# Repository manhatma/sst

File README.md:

Sufni Suspension Telemetry
==========================

Sufni\* Suspension Telemetry is a mountain bike suspension telemetry system that
was born out of sheer curiosity. The [data acquisition unit](https://github.com/sghctoma/sst/wiki/02-Data-Acquisition-Unit) is built around the
Raspberry Pi Pico W and uses affordable off-the-shelf components, so anybody
with a bit of soldering skills can build it.

Contrary to most (all?) suspension telemetry systems, Sufni uses rotary encoders
to measure movement. They are cheap, reasonably accurate, and can reach pretty
high sample rates. An additional benefit is that on some frames they are easier
to attach to rear shocks than linear sensors, because they can fit into much
tigther spaces.

The DAQ uses a WiFi network to send recorded sessions to the backend server.
When processing is done, data can be analyzed on the [web user interface](https://github.com/sghctoma/sst/wiki/03-Dashboard) that
provides plots useful for setting up the spring rate, damping and the bike's
overall balance. GPX tracks can also be uploaded, and MP4 videos can be opened
from the local machine. These are synchronized to the travel plot, so you can
easily find how your suspension behaved on a certain part of the trail.

The user interface has two additional functionalities:

 - New bike setups can be created, and they can be associated with a DAQ unit
   based on the Pico's uniqe identifer.
 - Normalized (travel percentage, or a number between 0 and 1) data can also be
   [imported](https://github.com/sghctoma/sst/wiki/04-Importing-normalized-data) from CSV files, so you can use the webapp without being tied to
   Sufni's hardware.

Please refer to the wiki for a [quickstart guide](https://github.com/sghctoma/sst/wiki/01-Quickstart-guide), build instructions, and a full
tour on the user interface, plots etc.

\* *The word "sufni" (pronounced SHOOF-nee) means tool shed in Hungarian, but
also used as an adjective denoting something as DIY, garage hack, etc.*

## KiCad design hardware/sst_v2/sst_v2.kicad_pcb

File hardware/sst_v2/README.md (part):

# SST v2 Mainboard — Rev. 3 (KiCad)

DAQ-Mainboard für Sufni Suspension Telemetry: 24-bit-ADC für Fork- und Shock-Poti,
Takt für vier IMUs, microSD, RTC, Pico 2 W. Entwurfsgrundlage und Begründungen:
`firmware/docs/plan-ads131m04-icm42686.md`.

```bash
open -a "KiCad" /Users/niels/Telemetry/sst/hardware/sst_v2/sst_v2.kicad_pro
```

Nur diesen Ordner bearbeiten. Vor Skript-Änderungen KiCad schließen
(`~*.lck`), sonst überschreibt die GUI beim Speichern.

## Platine

60 × 90 mm, 4 Lagen, 1,6 mm FR4, ENIG. 4× M3-NPTH (H1–H4).

Platzierung:

- Oben: Pico 2 W auf Buchsenleisten, U1 bei (134,4 / 59,8). Der Körper liegt bei x 84,7–137,1 mm. Das Antennenende liegt am linken Platinenrand (Kante 84,5 mm), wie Raspberry Pi es empfiehlt. Das USB-Ende liegt bei x 137,1 mm. Vor dem USB-Ende liegen 7,4 mm Platine (Rand 144,5 mm).
- Links: Poti-Eingang (J_POT1 am Rand, ESD D2–D4, CMCs), darunter Analogblock (LDO, ADC, Opamp, RC-Netz). Der Analogblock liegt weit weg von Funkmodul und SMPS des Pico.
- Mitte: RTC-Batterie BT1 unter dem Pico, Öffnung zum Pico. Der Bereich zwischen BT1 und den Pico-Buchsenleisten ist frei von Bauteilen, damit die Zelle heraus- und hineingleitet.
- Rechts: OLED- und Taster-Stecker am Rand neben ihren Pico-Pins, Buzzer BZ1, Stromversorgung (D1, D_VSYS1, C26), microSD. Der Körper von J_SD1 endet 0,25 mm vor der Platinenkante.
- Oberkante (x 113–123,6 mm, y 48,3–55,2 mm, zwischen Q_RP1 und J_DEBUG1, außerhalb des Pico): Lader U_CHG1 mit C_CHG1/C_CHG2, R_PROG, R_STAT1/R_STAT2. Thermalfläche: Zone „Lader Thermal“ (GND, F.Cu, Priorität 2, volle Anbindung) über den Laderbereich und den Streifen über J_DEBUG1, gefüllt 0,77 cm² zusammenhängend (0,49 cm² im Laderbereich). Sechs GND-Vias 0,6/0,3 mm links neben dem VSS-Pad (Pin 2) zur GND-Lage In1. +VBUS und +VBAT kommen auf B.Cu, F.Cu bleibt dort fast ganz GND.
- Unter dem Pico: R50 (ADC_RST) bei (110,0 / 62,3) neben GP7 (Pin 10). Soft-Power-Steuerung (U_PWR1, C_PWR1, Q_PWR2, Q_PWR3, R_PWR2–R_PWR4, D_PWR1) und Fuel Gauge (U_FG1, C_FG1) zwischen den Buchsenleisten bei x 120–135 mm, y 61–74 mm (Bauhöhe ≤ 1,1 mm, Buchsenleisten 8,5 mm). `sst_v2.kicad_dru` erlaubt die Courtyard-Überdeckung mit U1 nur für diese Teile.
- Unter der unteren Pico-Buchsenleiste (außerhalb des Pico): Lastschalter Q_PWR1 (119,6 / 82,1) mit Gate-Pull-up R_PWR1 (122,9 / 82,1), direkt vor C26.
- Pico-Antenne (Ende gegenüber USB, x < 94 mm, am linken Rand): Rule Area „Pico antenna: keepout“ auf allen Kupferlagen, ohne Leiterbahnen, Vias und Pours. Sie deckt den Raum zwischen den Buchsenleisten (x 84,5–94,0 mm, y 61,3–76,1 mm) und das Pico-Ende über die volle Breite ab (x 84,5–85,1 mm, y 57,1–80,2 mm). Der Rand von 1 mm liegt außerhalb der Platine, die Fläche endet an der Kante. Die Streifen der Buchsenleisten bleiben frei, damit die Leitungen an Pin 17–24 nach außen laufen. In1 (GND) und In2 (+3V3_DIG) haben dort eine Aussparung.
- Fiducials FID1–FID3 (1 mm, Maske 3 mm) auf F.Cu: (135,95 / 54,8), (89,5 / 106,8), (136,95 / 101,3). Alle ≥ 5 mm von der Kante, außerhalb von Pico und Steckern.
- Montagelöcher: Alle Courtyards liegen ≥ 3,5 mm von der Bohrungsmitte (Platz für Schraubenkopf oder Scheibe Ø 7 mm).
- Unten: IMU-Stecker, Taktteiler und Taktpuffer.
- Digitalleitungen (IMU, SD, UI) laufen außerhalb des Analogblocks. Die ADC-SPI-Leitungen laufen im Poti-Block nur auf B.Cu, getrennt durch die GND-Lage In1.

| Lage | Inhalt |
|---|---|
| F.Cu | Bauteile, Signale, GND-Pour |
| In1.Cu | GND, durchgehend |
| In2.Cu | +3V3_DIG; Insel +3V0_ANA unter der analogen Seite von LDO/ADC/Opamp (x 94,3–108,5 mm, y 112,2–132,5 mm, dazu Streifen y 107,8–112,2 mm ab x 84,9 mm). Die digitale Seite von LDO und ADC (x < 94,3 mm) liegt über +3V3_DIG. |
| B.Cu | Signale, GND-Pour |

Fertigungsregeln (PCBWay): Leiterbahn/Abstand ≥ 0,2 mm, Via 0,6/0,3 mm (+3V3_DIG: 0,7/0,4 mm,
Power: 0,8/0,4 mm), Via-Restring ≥ 0,15 mm, Kupfer–Kante ≥ 0,3 mm, Lötstopp-Steg ≥ 0,1 mm
(grüner Lötstopp). Silkscreen: Strichbreite ≥ 0,15 mm, Texthöhe ≥ 0,8 mm (PCBWay-Minimum). `sst_v2.kicad_pro`
prüft Restring und Textstrich mit 0,15 mm, Texthöhe mit 0,8 mm.

## Schaltung

| Block | Bauteile | Kurzbeschreibung |
|---|---|---|
| ADC | U2 ADS131M04 | CH0 Fork, CH1 Shock, CH2 Poti-Speisung (ratiometrisch), CH3 an GND. AVDD 3,0 V, DVDD = Netz +3V3_DVDD aus +3V3_DIG über FB1 (Logikpegel = Pico-Pegel, PWR_FLAG hinter FB1). CAP 220 nF. SYNC/RESET (ADC_RST) über R50 100 Ω an GP7 (ADC_RST_MCU), Pull-up R1, C4. |
| Analog-LDO | U_ANA_LDO1 TPS7A4700 (RGW) | 3,3 V → 3,0 V, ANY-OUT: nur 1P6V (Pin 8) an GND, übrige ANY-Pins offen. SENSE an OUT. NR 10 nF (C25), IN 10 µF (C22), OUT 22 µF (C6). |
| Poti-Speisung | U_AAF1 TLV4333 (A), R32/R33 20k/10k 0,1 %, C35 | 1,0 V Referenz, gepuffert, 47 Ω (R34) auf POT_EXC, Messung über R35/C36 an AIN2P. |
| Schleifer | U_AAF1 (B, C), R36/R37, R8/R14, C9/C12 | Opamp-Puffer, danach 1 kΩ + 10 nF an AINxP. AINxN = Poti-Masse (Remote Sense), R9/R15 0 Ω als Sternpunkt. |
| Poti-Stecker | J_POT1 JST-SH 6 → HR30 6p | 1 POT_EXC, 2 Fork-Schleifer, 3 Fork-Masse, 4 Shock-Schleifer, 5 Shock-Masse, 6 Schirm/GND. ESD D2–D4, CMC L_FORK/L_SHOCK (DLW5BTM251SQ2L). |
| Takt | Y1 ECS-2520MVLC 8,192 MHz, U_DIV1 74HC4040, U_CLKBUF1 74LVC125 | XO → 33 Ω → ADC CLKIN; XO → 4040 Q7 = 32,000 kHz → 2 Puffer → 33 Ω → IMU-CLKIN A/B. |
| IMU | J_IMU_A1/B1 JST-SH 12 → HR30 12p | 1 IMU_3V3 (FB2), 3 SCLK, 5 MOSI, 7 MISO, 8 CLKIN, 10/11 CS, 2/4/6/9/12 GND. 33 Ω in allen DAQ-Ausgängen. |
| Strom | J_BAT1, Q_RP1, Q_PWR1, D1, D_VSYS1 | LiPo (JST-PH) → Q_RP1 DMG2305UX (Verpolschutz) → +VBAT → Q_PWR1 DMG2305UX (Soft-Power-Schalter) → +VBAT_SW (TVS D1, C26–C28) → D_VSYS1 PMEG3020EH → VSYS. D_VSYS1 verhindert, dass USB-VBUS direkt in den Akku speist. Kein externer Schalter mehr (J_PWR1 entfällt). |
| Soft-Power | U_PWR1 MAX16150AUT+T, Q_PWR1 DMG2305UX, Q_PWR2/Q_PWR3 2N7002, R_PWR1–R_PWR4 100k, C_PWR1 100 nF, D_PWR1 RB751S40 | U_PWR1 VCC an +VBAT. Taster SW_L1 → PWR_BTN → PB_IN (interner Pull-up 1,2–2,0 MΩ an VCC). Drücken > 50 ms: OUT (PSW_EN) high → Q_PWR2 zieht PSW_GATE auf GND → Q_PWR1 leitet. R_PWR1 hält Q_PWR1 sonst aus, R_PWR2 hält Q_PWR2 aus, solange OUT undefiniert ist. Aus per Firmware: GP28 (PWR_OFF) high → Q_PWR3 zieht ~CLR low → OUT low. R_PWR4 hält Q_PWR3 ohne Firmware aus. ~CLR-Pull-up R_PWR3 an OUT (Datenblatt-Empfehlung): kein VBAT-Pegel an einem GPIO. Halten > 8 s (Version A): OUT low, Hardware-Aus. ~INT offen. BTN_L (GP4, R27 10k an +3V3_DIG) liegt über D_PWR1 (Anode BTN_L, Kathode PWR_BTN) am Taster: SW_L1 bleibt UI-Taste. |
| Fuel Gauge | U_FG1 MAX17048G+T10, C_FG1 100 nF | VDD (Messeingang) und CELL an +VBAT, dauerhaft versorgt. I2C 0x36 am PIO-I2C (DISP_SDA/DISP_SCL, R25/R26). CTG, QSTRT, EP an GND, ~ALRT offen (kein GPIO frei). |
| Lader | U_CHG1 MCP73831T-2ACI/OT, C_CHG1/C_CHG2 4,7 µF, R_PROG 3,3k, R_STAT1/R_STAT2 10k/10k | Platz an der Oberkante außerhalb des Pico, mit Thermalfläche (GND-Zone 0,77 cm² an VSS, 6 Vias zu In1). VDD an +VBUS (Pico Pin 40), Ausgang an +VBAT (vor dem Schalter): Laden auch bei ausgeschaltetem Gerät (Q_PWR1 offen). 4,20 V, 300 mA (I = 1000 V / R_PROG; 500 mA mit 2,0k). STAT über Teiler 10k/10k an GP6 (CHG_STAT): Laden = 0 V, fertig = 0,5 × VBUS (2,5 V bei 5,0 V, max. 2,6 V bei 5,25 V), ohne VBUS hochohmig → 0 V. USB kommt über ein Kabel von einer Gehäusebuchse in die Micro-USB-Buchse des Pico. |
| RTC | U3 DS3231SN, BT1 CR1220 | VBAT direkt an der Zelle, RST offen. I2C gemeinsam mit OLED und U_FG1 (PIO, R25/R26 4,7k). |
| microSD | J_SD1 DM3AT | SPI0. Pull-ups: SD_CS 10k (R31), DAT1 47k (R48), DAT2 47k (R49). |
| UI | SW_L1/SW_R1 (JST-SH 2), BZ1 PS1240P02BT, J_OLED1, J_DEBUG1 | Taster mit 10k-Pull-up. SW_L1 ist zusätzlich die Power-Taste (siehe Soft-Power). Buzzer über 47 Ω an GP22. J_DEBUG1: 1 RX (GP1), 2 TX (GP0), 3 GND. SWD direkt am Pico. |
| MCU | U1 Pico 2 W | Steckt in 2× 1×20-Buchsenleisten (8,5 mm). 3V3_EN offen (interner Pull-up). |

### Pico-Pinbelegung

| GP | Netz | GP | Netz |
|---:|---|---:|---|
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
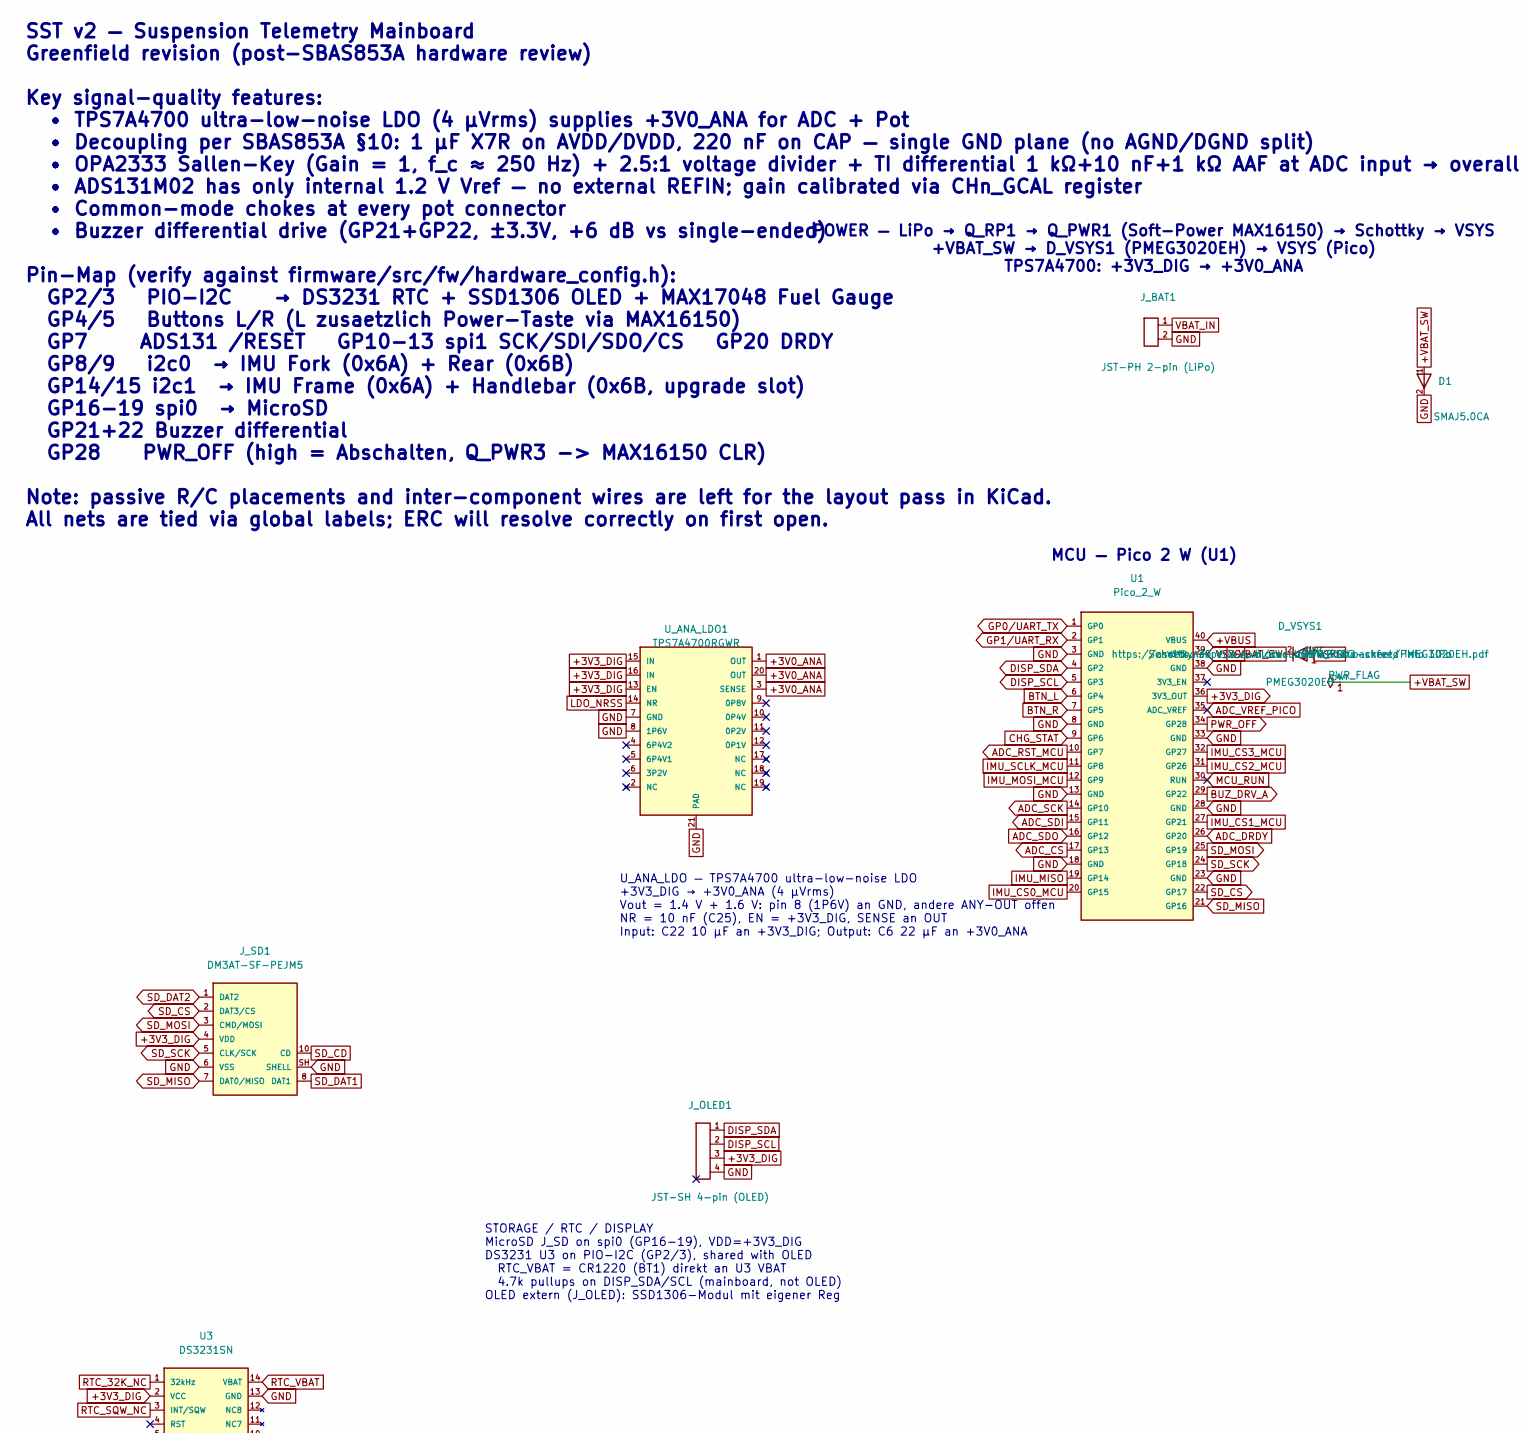
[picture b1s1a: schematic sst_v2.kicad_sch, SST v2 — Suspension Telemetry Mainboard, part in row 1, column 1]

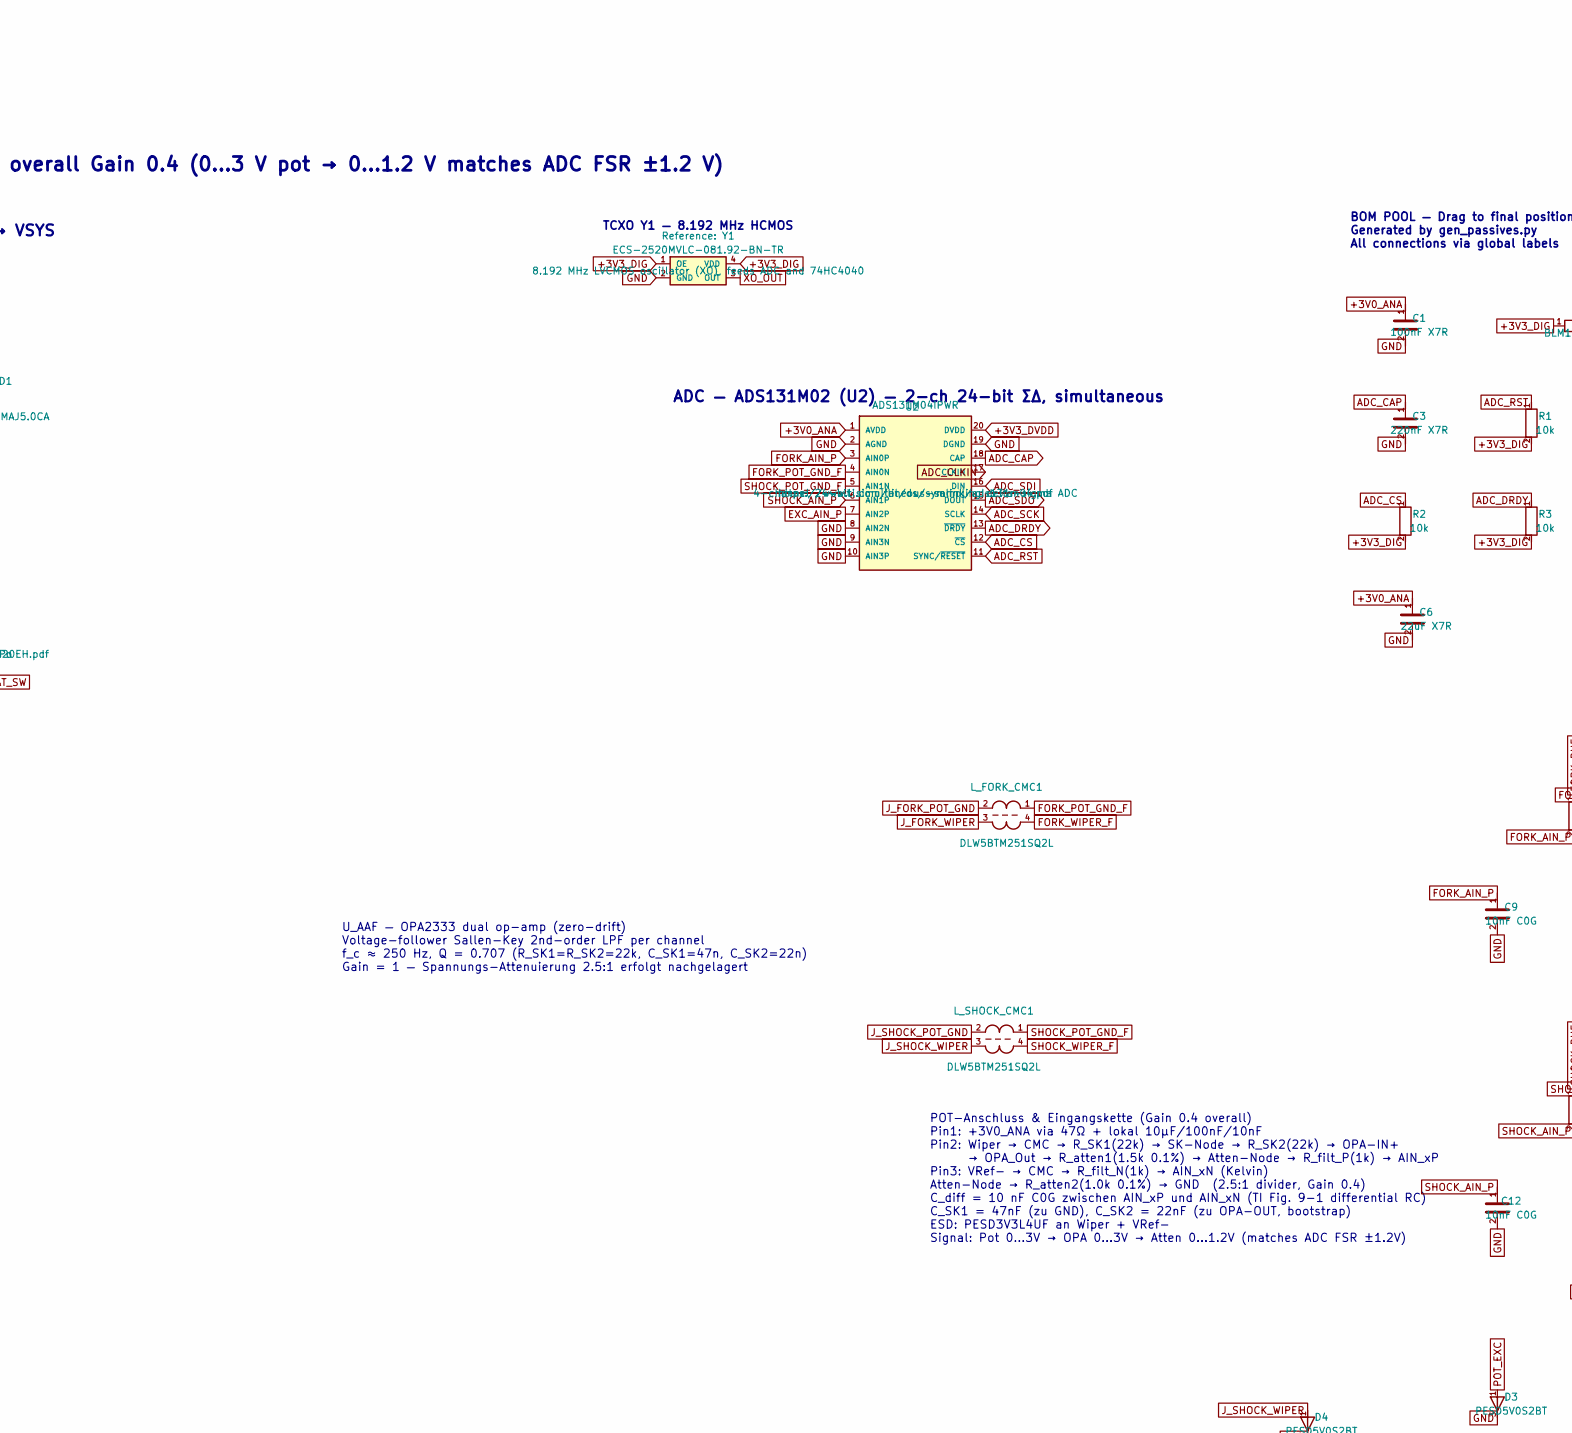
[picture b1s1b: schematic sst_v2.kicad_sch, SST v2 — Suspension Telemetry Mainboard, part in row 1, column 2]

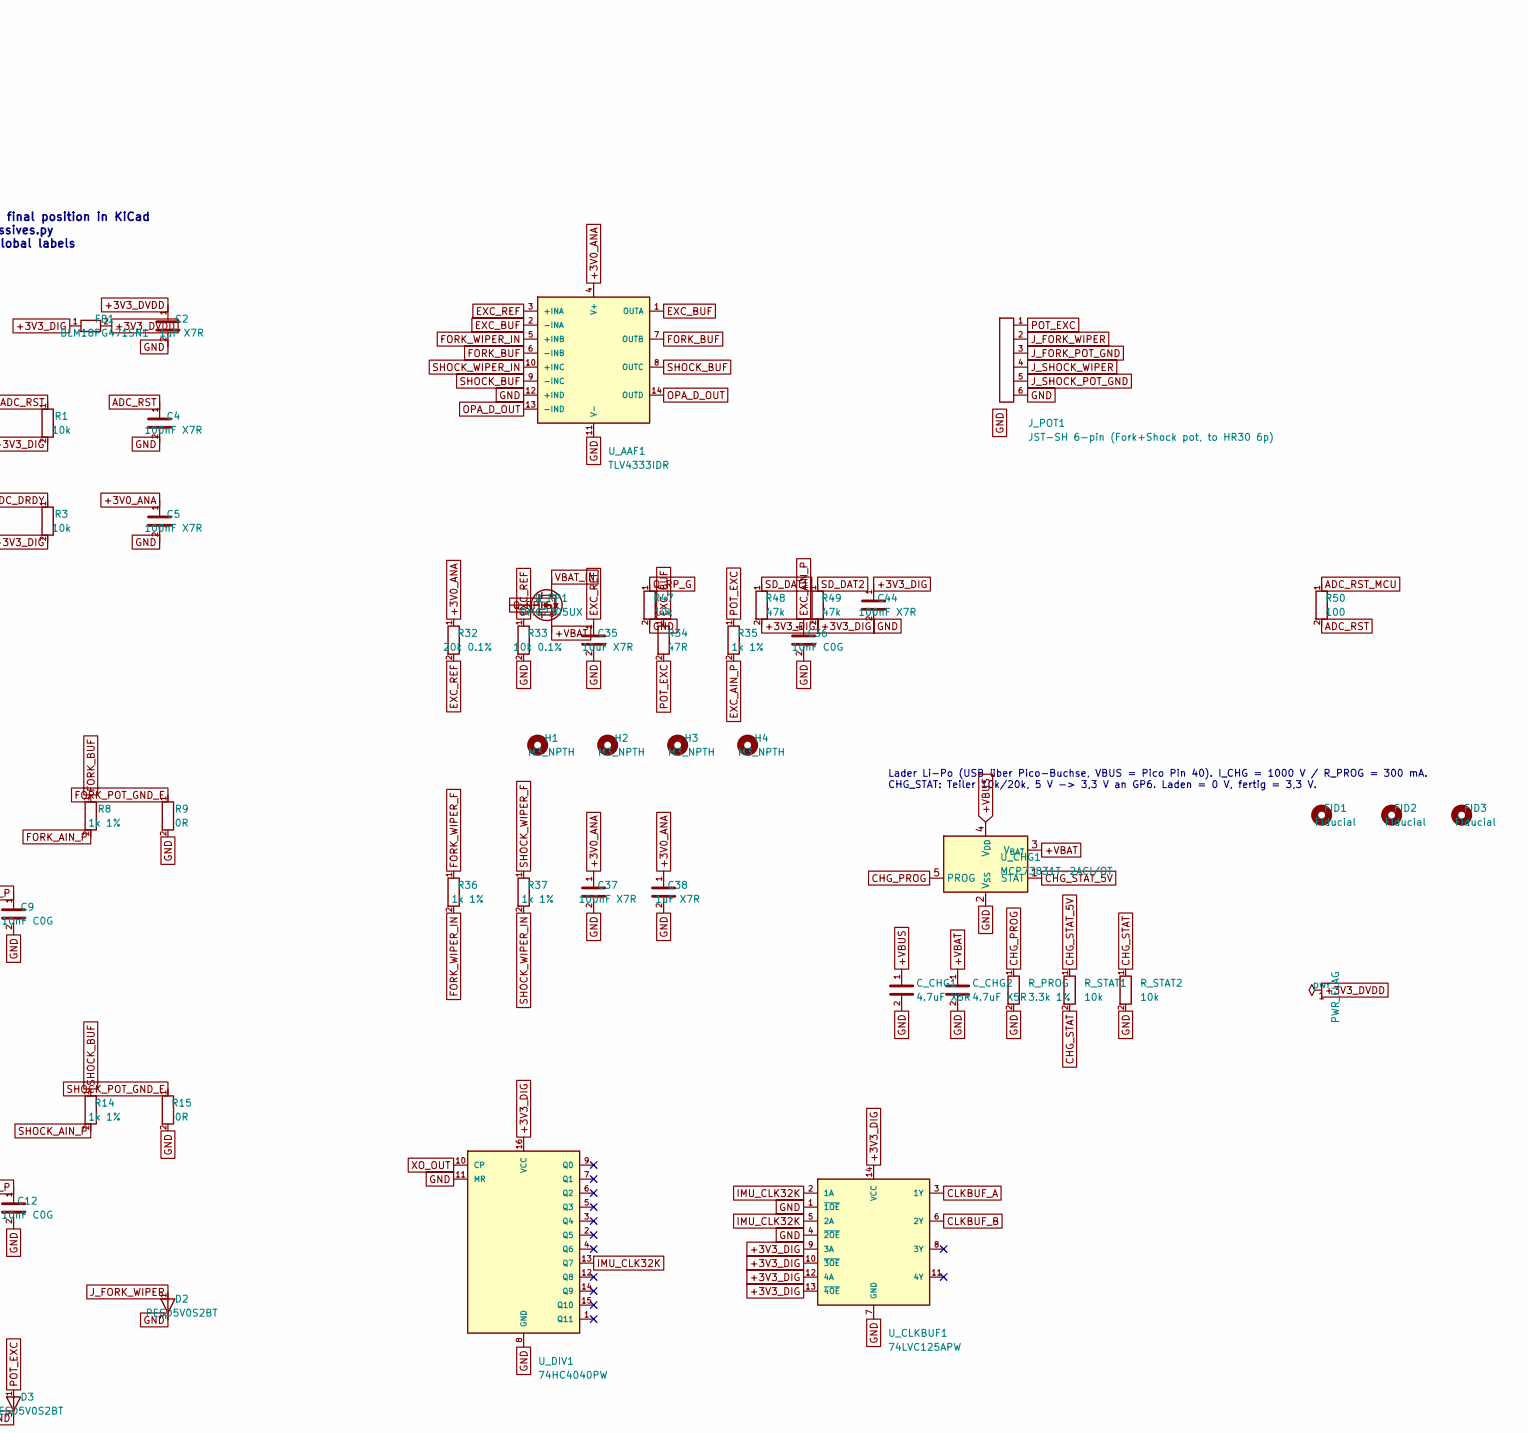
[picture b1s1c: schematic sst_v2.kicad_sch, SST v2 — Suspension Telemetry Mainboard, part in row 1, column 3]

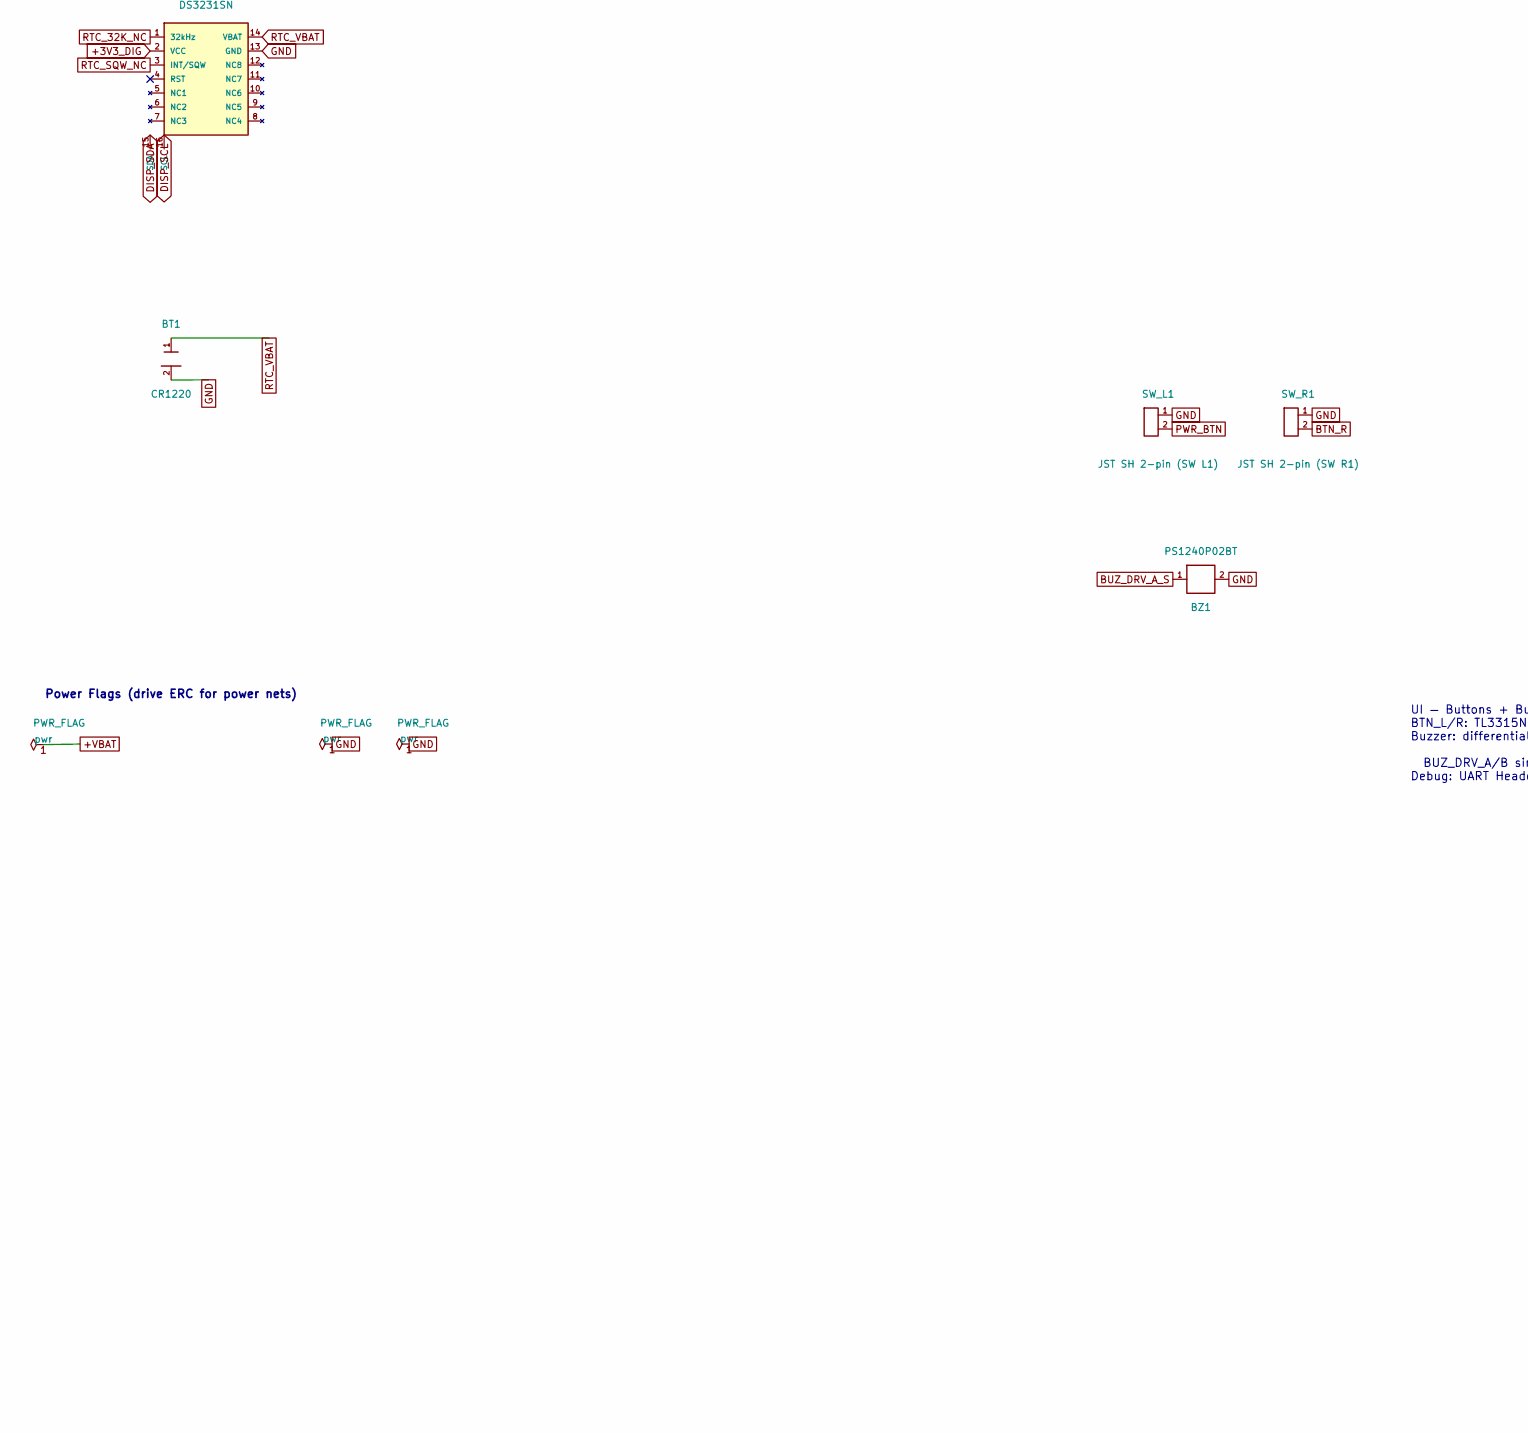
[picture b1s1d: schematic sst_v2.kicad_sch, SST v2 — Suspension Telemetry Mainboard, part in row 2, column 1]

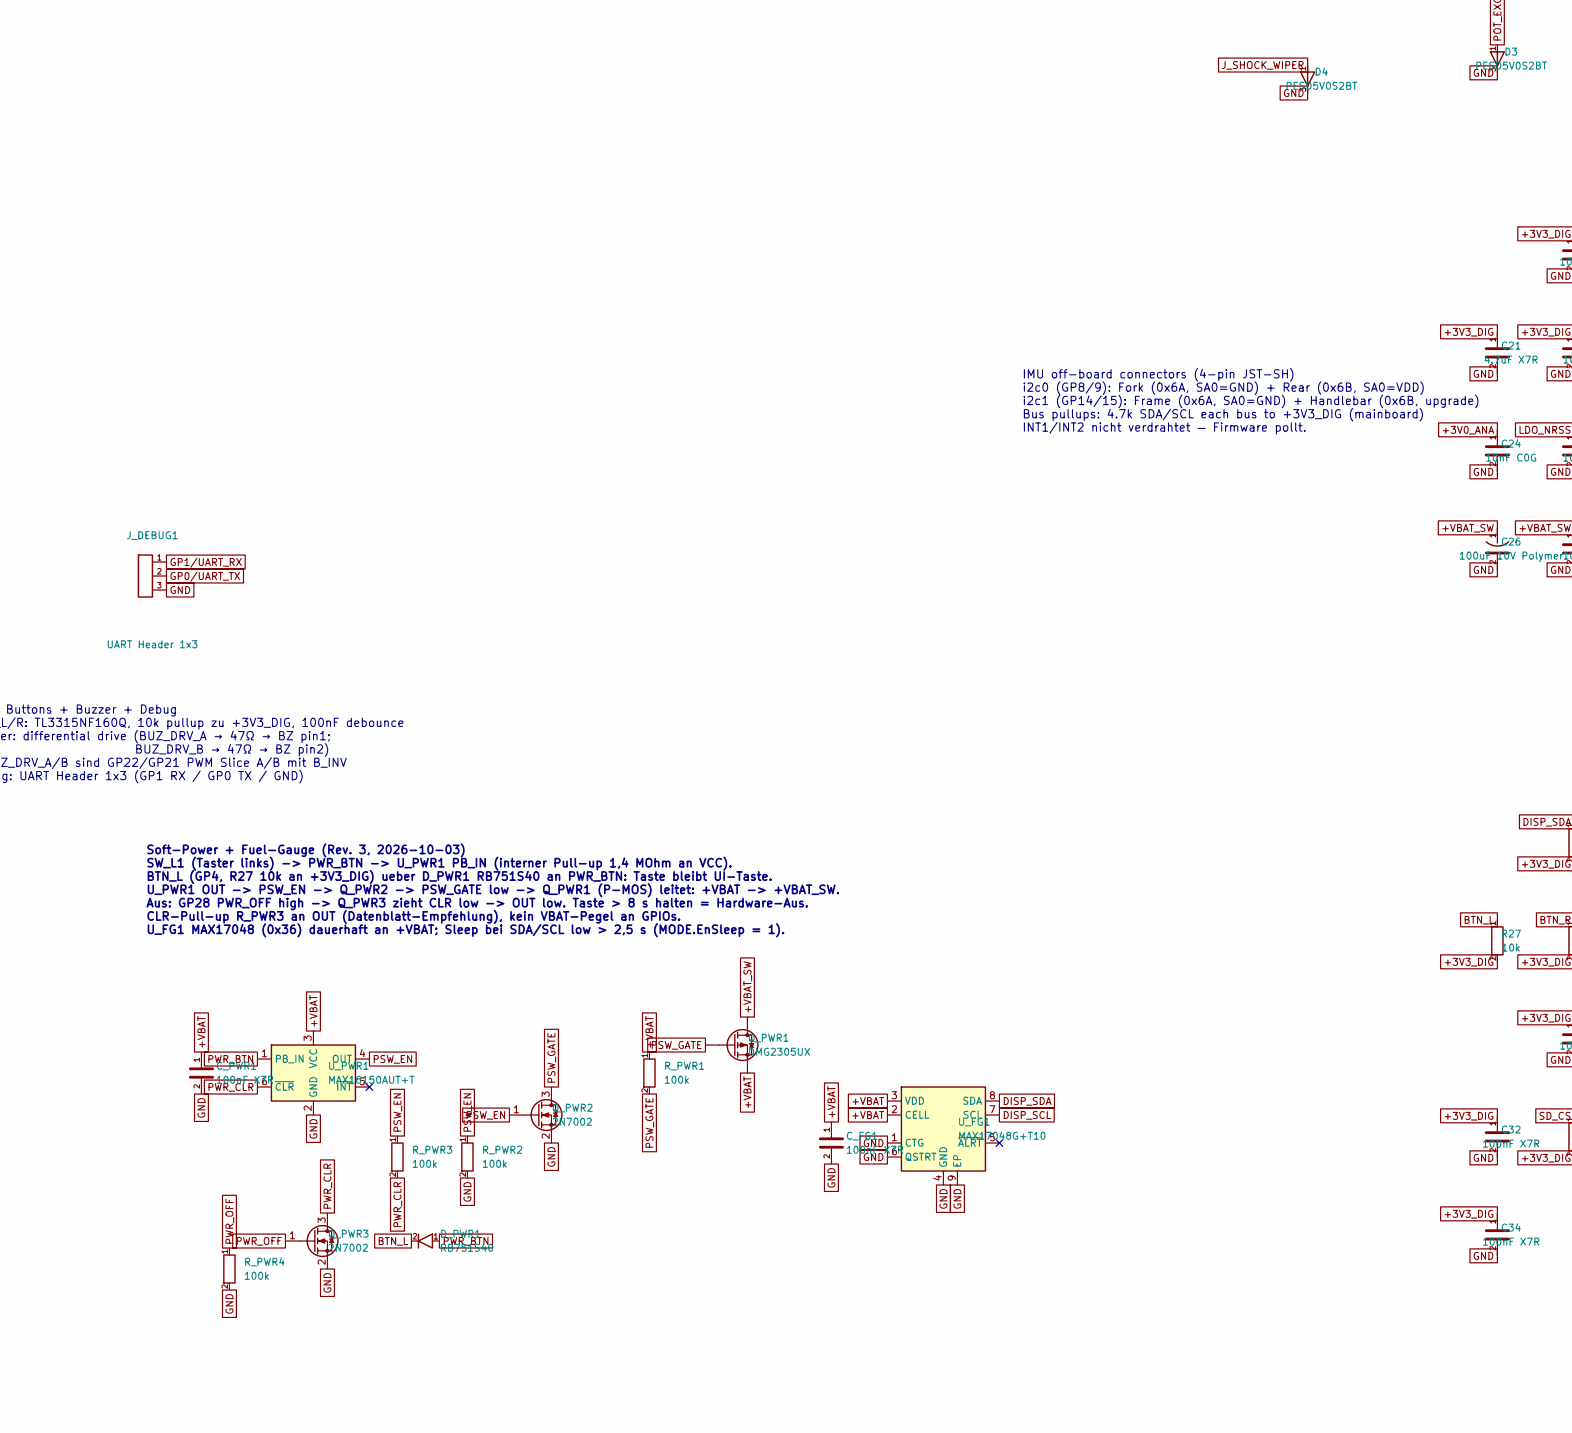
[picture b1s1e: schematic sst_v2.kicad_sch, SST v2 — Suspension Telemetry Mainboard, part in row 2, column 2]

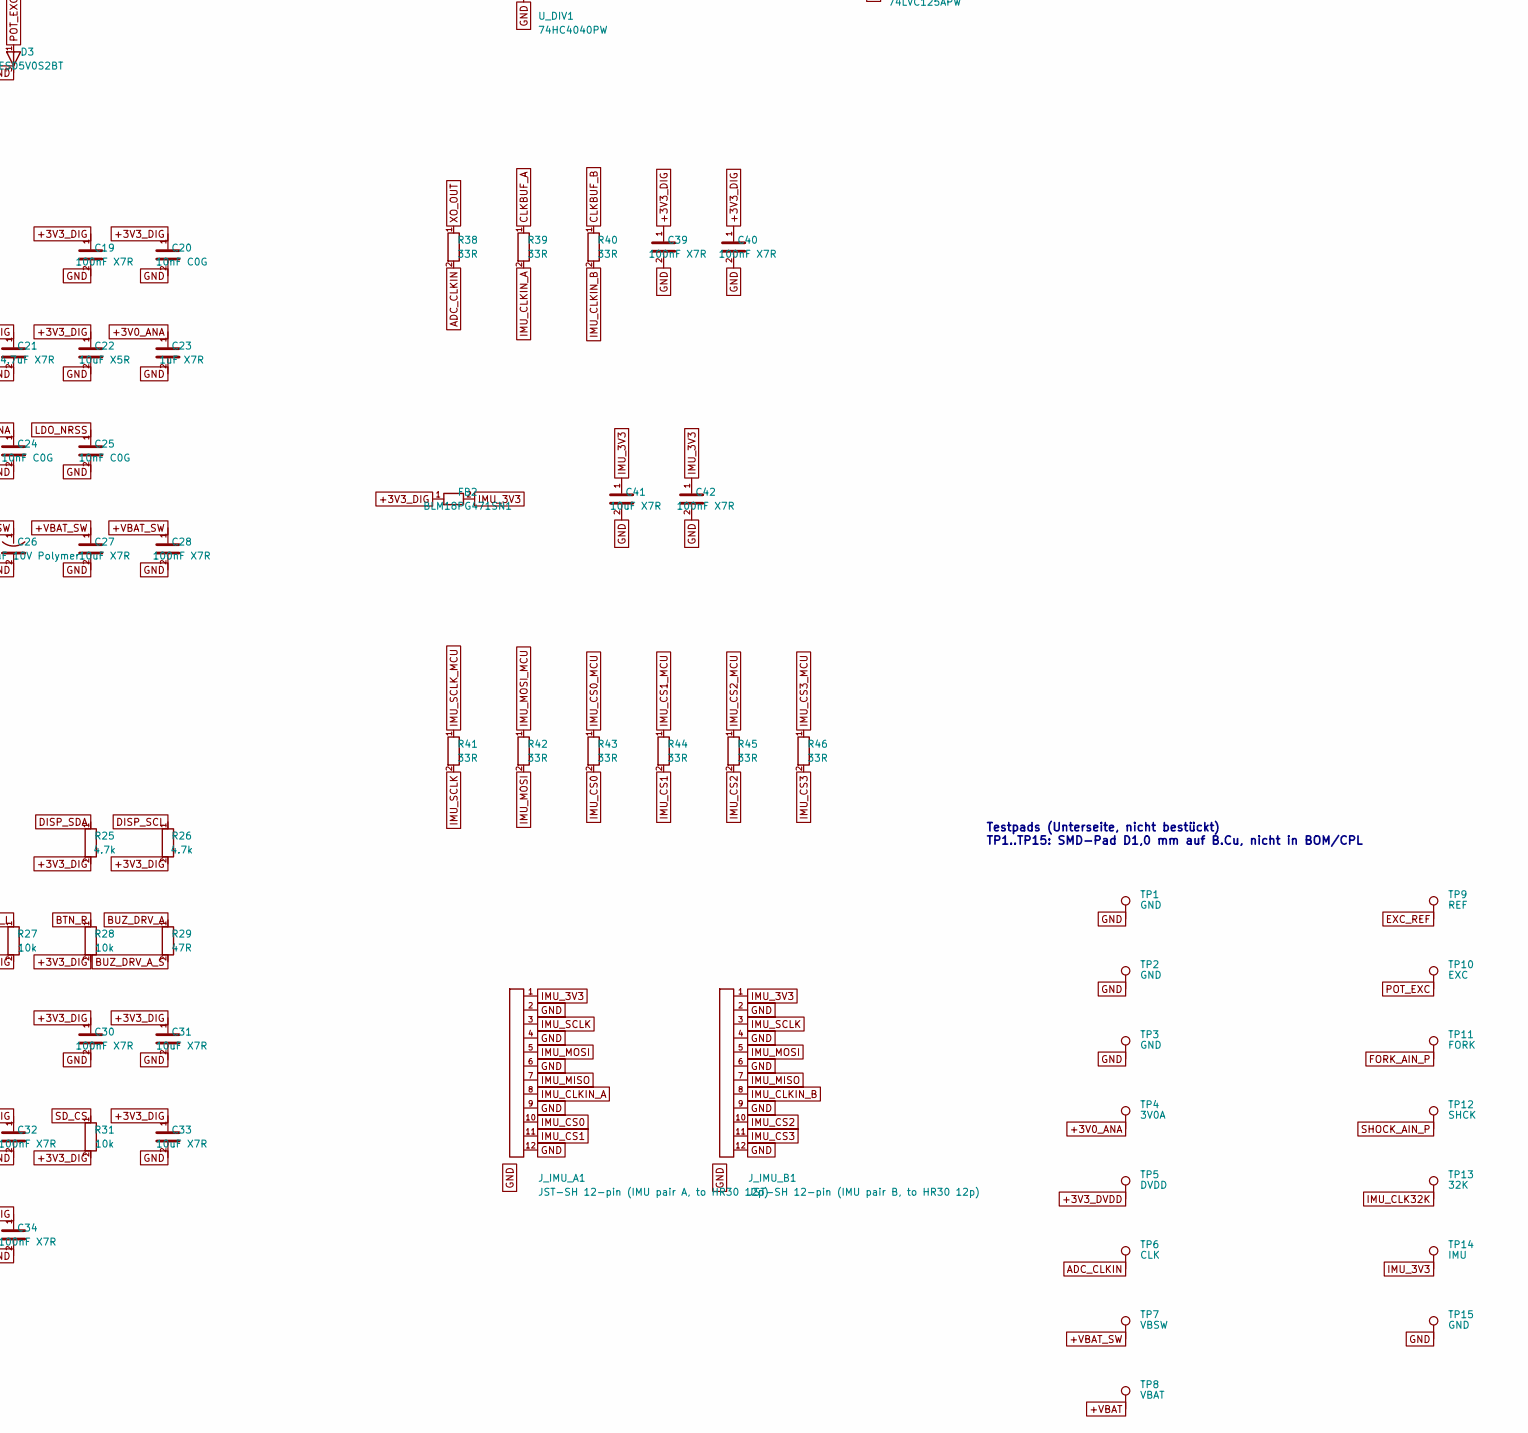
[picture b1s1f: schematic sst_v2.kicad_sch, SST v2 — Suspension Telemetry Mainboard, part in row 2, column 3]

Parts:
BT1: CR1220; BatteryHolder_Keystone_3001_1x12mm
BZ1: PS1240P02BT; Buzzer_TDK_PS1240P02BT_D12.2mm_H6.5mm
C1, C4, C5, C19, C28, C30, C32, C34, C37, C39, C40, C42, C44: 100nF X7R; C_0603_1608Metric
C2, C23, C38: 1uF X7R; C_0603_1608Metric
C3: 220nF X7R; C_0603_1608Metric
C6: 22uF X7R; C_0805_2012Metric
C9, C12, C20, C24, C25, C36: 10nF C0G; C_0603_1608Metric
C21: 4.7uF X7R; C_0805_2012Metric
C22: 10uF X5R; C_0603_1608Metric
C26: 100uF 10V Polymer; CP_EIA-7343-31_Kemet-D
C27, C31, C33, C35, C41: 10uF X7R; C_0805_2012Metric
C_CHG1, C_CHG2: 4.7uF X5R; C_0805_2012Metric
C_FG1: 100nF X7R; C_0603_1608Metric
C_PWR1: 100nF X7R; C_0603_1608Metric
D1: SMAJ5.0CA; D_SMA
D2, D3, D4: PESD5V0S2BT; SOT-23
D_PWR1: RB751S40; D_SOD-523
D_VSYS1: PMEG3020EH; D_SOD-123F
FB1, FB2: BLM18PG471SN1; L_0603_1608Metric
FID1, FID2, FID3: Fiducial; Fiducial_1mm_Mask3mm
H1, H2, H3, H4: M3_NPTH; MountingHole_3.2mm_M3
J_BAT1: JST-PH 2-pin (LiPo); JST_PH_B2B-PH-K_1x02_P2.00mm_Vertical
J_DEBUG1: UART Header 1x3; PinHeader_1x03_P2.54mm_Vertical
J_IMU_A1: JST-SH 12-pin (IMU pair A, to HR30 12p); JST_SH_BM12B-SRSS-TB_1x12-1MP_P1.00mm_Vertical
J_IMU_B1: JST-SH 12-pin (IMU pair B, to HR30 12p); JST_SH_BM12B-SRSS-TB_1x12-1MP_P1.00mm_Vertical
J_OLED1: JST-SH 4-pin (OLED); JST_SH_BM04B-SRSS-TB_1x04-1MP_P1.00mm_Vertical
J_POT1: JST-SH 6-pin (Fork+Shock pot, to HR30 6p); JST_SH_BM06B-SRSS-TB_1x06-1MP_P1.00mm_Vertical
J_SD1: DM3AT-SF-PEJM5; microSD_HC_Hirose_DM3AT-SF-PEJM5
L_FORK_CMC1: DLW5BTM251SQ2L; L_CommonModeChoke_Murata_DLW5BTMxxxSQ2x_5x5mm
L_SHOCK_CMC1: DLW5BTM251SQ2L; L_CommonModeChoke_Murata_DLW5BTMxxxSQ2x_5x5mm
Q_PWR1: DMG2305UX; SOT-23
Q_PWR2, Q_PWR3: 2N7002; SOT-23
Q_RP1: DMG2305UX; SOT-23
R1, R2, R3, R27, R28, R31, R47: 10k; R_0603_1608Metric
R8, R14, R35, R36, R37: 1k 1%; R_0603_1608Metric
R9, R15: 0R; R_0603_1608Metric
R25, R26: 4.7k; R_0603_1608Metric
R29, R34: 47R; R_0603_1608Metric
R32: 20k 0.1%; R_0603_1608Metric
R33: 10k 0.1%; R_0603_1608Metric
R38, R39, R40, R41, R42, R43, R44, R45, R46: 33R; R_0603_1608Metric
R48, R49: 47k; R_0603_1608Metric
R50: 100; R_0603_1608Metric
R_PROG: 3.3k 1%; R_0603_1608Metric
R_PWR1, R_PWR2, R_PWR3, R_PWR4: 100k; R_0603_1608Metric
R_STAT1, R_STAT2: 10k; R_0603_1608Metric
SW_L1: JST SH 2-pin (SW L1); JST_SH_BM02B-SRSS-TB_1x02-1MP_P1.00mm_Vertical
SW_R1: JST SH 2-pin (SW R1); JST_SH_BM02B-SRSS-TB_1x02-1MP_P1.00mm_Vertical
TP1, TP2, TP3, TP15: GND; TestPoint_Pad_D1.0mm
TP4: 3V0A; TestPoint_Pad_D1.0mm
TP5: DVDD; TestPoint_Pad_D1.0mm
TP6: CLK; TestPoint_Pad_D1.0mm
TP7: VBSW; TestPoint_Pad_D1.0mm
TP8: VBAT; TestPoint_Pad_D1.0mm
TP9: REF; TestPoint_Pad_D1.0mm
TP10: EXC; TestPoint_Pad_D1.0mm
TP11: FORK; TestPoint_Pad_D1.0mm
TP12: SHCK; TestPoint_Pad_D1.0mm
TP13: 32K; TestPoint_Pad_D1.0mm
TP14: IMU; TestPoint_Pad_D1.0mm
U1: Pico_2_W; RaspberryPi_Pico_Common_THT
U2: ADS131M04IPWR; TSSOP-20_4.4x6.5mm_P0.65mm
U3: DS3231SN; SOIC-16W_7.5x10.3mm_P1.27mm
U_AAF1: TLV4333IDR; SOIC-14_3.9x8.7mm_P1.27mm
U_ANA_LDO1: TPS7A4700RGWR; Texas_RGW0020A_VQFN-20-1EP_5x5mm_P0.65mm_EP3.15x3.15mm
U_CHG1: MCP73831T-2ACI/OT; SOT-23-5
U_CLKBUF1: 74LVC125APW; TSSOP-14_4.4x5mm_P0.65mm
U_DIV1: 74HC4040PW; TSSOP-16_4.4x5mm_P0.65mm
U_FG1: MAX17048G+T10; TDFN-8-1EP_2x2mm_P0.5mm_EP0.8x1.2mm
U_PWR1: MAX16150AUT+T; SOT-23-6
Y1: ECS-2520MVLC-081.92-BN-TR; Oscillator_SMD_ECS_2520MV-xxx-xx-4Pin_2.5x2.0mm

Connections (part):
+3V0_ANA: C1.1, C5.1, C6.1, C23.1, C24.1, C37.1, C38.1, R32.1, TP4.1, U2.1 (AVDD), U_AAF1.4 (V+), U_ANA_LDO1.1 (OUT), U_ANA_LDO1.3 (SENSE), U_ANA_LDO1.20 (OUT)
+3V3_DIG: C19.1, C20.1, C21.1, C22.1, C30.1, C31.1, C32.1, C33.1, C34.1, C39.1, C40.1, C44.1, FB1.1, FB2.1, J_OLED1.3, J_SD1.4 (VDD), R1.2, R2.2, R3.2, R25.2, R26.2, R27.2, R28.2, R31.2, R48.2, R49.2, U1.36 (3V3_OUT), U3.2 (VCC), U_ANA_LDO1.13 (EN), U_ANA_LDO1.15 (IN), U_ANA_LDO1.16 (IN), U_CLKBUF1.9 (3A), U_CLKBUF1.10 (~3OE), U_CLKBUF1.12 (4A), U_CLKBUF1.13 (~4OE), U_CLKBUF1.14 (VCC), U_DIV1.16 (VCC), Y1.1 (OE), Y1.4 (VDD)
+3V3_DVDD: C2.1, FB1.2, TP5.1, U2.20 (DVDD)
+VBAT: C_CHG2.1, C_FG1.1, C_PWR1.1, Q_PWR1.2 (S), Q_RP1.2 (S), R_PWR1.1, TP8.1, U_CHG1.3 (V_{BAT}), U_FG1.2 (CELL), U_FG1.3 (VDD), U_PWR1.3 (VCC)
+VBAT_SW: C26.1, C27.1, C28.1, D1.1 (K), D_VSYS1.2 (A), Q_PWR1.3 (D), TP7.1
+VBUS: C_CHG1.1, U1.40 (VBUS), U_CHG1.4 (V_{DD})
ADC_CAP: C3.1, U2.18 (CAP)
ADC_CLKIN: R38.2, TP6.1, U2.17 (CLKIN)
ADC_CS: R2.1, U1.17 (GP13), U2.12 (~CS)
ADC_DRDY: R3.1, U1.26 (GP20), U2.13 (~DRDY)
ADC_RST: C4.1, R1.1, R50.2, U2.11 (SYNC/~RESET)
ADC_RST_MCU: R50.1, U1.10 (GP7)
ADC_SCK: U1.14 (GP10), U2.14 (SCLK)
ADC_SDI: U1.15 (GP11), U2.16 (DIN)
ADC_SDO: U1.16 (GP12), U2.15 (DOUT)
ADC_VREF_PICO: U1.35 (ADC_VREF)
BTN_L: D_PWR1.2 (A), R27.1, U1.6 (GP4)
BTN_R: R28.1, SW_R1.2, U1.7 (GP5)
BUZ_DRV_A: R29.1, U1.29 (GP22)
BUZ_DRV_A_S: BZ1.1 (+), R29.2
CHG_PROG: R_PROG.1, U_CHG1.5 (PROG)
CHG_STAT: R_STAT1.2, R_STAT2.1, U1.9 (GP6)
CHG_STAT_5V: R_STAT1.1, U_CHG1.1 (STAT)
CLKBUF_A: R39.1, U_CLKBUF1.3 (1Y)
CLKBUF_B: R40.1, U_CLKBUF1.6 (2Y)
DISP_SCL: J_OLED1.2, R26.1, U1.5 (GP3), U3.16 (SCL), U_FG1.7 (SCL)
DISP_SDA: J_OLED1.1, R25.1, U1.4 (GP2), U3.15 (SDA), U_FG1.8 (SDA)
EXC_AIN_P: C36.1, R35.2, U2.7 (AIN2P)
EXC_BUF: R34.1, U_AAF1.1 (OUTA), U_AAF1.2 (-INA)
EXC_REF: C35.1, R32.2, R33.1, TP9.1, U_AAF1.3 (+INA)
FORK_AIN_P: C9.1, R8.2, TP11.1, U2.3 (AIN0P)
FORK_BUF: R8.1, U_AAF1.6 (-INB), U_AAF1.7 (OUTB)
FORK_POT_GND_F: L_FORK_CMC1.1, R9.1, U2.4 (AIN0N)
FORK_WIPER_F: L_FORK_CMC1.4, R36.1
FORK_WIPER_IN: R36.2, U_AAF1.5 (+INB)
GND: BT1.2 (-), BZ1.2 (-), C1.2, C2.2, C3.2, C4.2, C5.2, C6.2, C9.2, C12.2, C19.2, C20.2, C21.2, C22.2, C23.2, C24.2, C25.2, C26.2, C27.2, C28.2, C30.2, C31.2, C32.2, C33.2, C34.2, C35.2, C36.2, C37.2, C38.2, C39.2, C40.2, C41.2, C42.2, C44.2, C_CHG1.2, C_CHG2.2, C_FG1.2, C_PWR1.2, D1.2 (A), D2.3 (A), D3.3 (A), D4.3 (A), J_BAT1.2, J_DEBUG1.3, J_IMU_A1.2, J_IMU_A1.4, J_IMU_A1.6, J_IMU_A1.9, J_IMU_A1.12, J_IMU_A1.MP, J_IMU_B1.2, J_IMU_B1.4, J_IMU_B1.6, J_IMU_B1.9, J_IMU_B1.12, J_IMU_B1.MP, J_OLED1.4, J_POT1.6, J_POT1.MP, J_SD1.6 (VSS), J_SD1.SH (SHELL), Q_PWR2.2 (S), Q_PWR3.2 (S), R9.2, R15.2, R33.2, R47.2, R_PROG.2, R_PWR2.2, R_PWR4.2, R_STAT2.2, SW_L1.1, SW_R1.1, TP1.1, TP2.1, TP3.1, TP15.1, U1.3 (GND), U1.8 (GND), U1.13 (GND)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
GP0/UART_TX: J_DEBUG1.2, U1.1 (GP0)
GP1/UART_RX: J_DEBUG1.1, U1.2 (GP1)
IMU_3V3: C41.1, C42.1, FB2.2, J_IMU_A1.1, J_IMU_B1.1, TP14.1
IMU_CLK32K: TP13.1, U_CLKBUF1.2 (1A), U_CLKBUF1.5 (2A), U_DIV1.13 (Q7)
IMU_CLKIN_A: J_IMU_A1.8, R39.2
IMU_CLKIN_B: J_IMU_B1.8, R40.2
IMU_CS0: J_IMU_A1.10, R43.2
IMU_CS0_MCU: R43.1, U1.20 (GP15)
IMU_CS1: J_IMU_A1.11, R44.2
IMU_CS1_MCU: R44.1, U1.27 (GP21)
IMU_CS2: J_IMU_B1.10, R45.2
IMU_CS2_MCU: R45.1, U1.31 (GP26)
IMU_CS3: J_IMU_B1.11, R46.2
IMU_CS3_MCU: R46.1, U1.32 (GP27)
IMU_MISO: J_IMU_A1.7, J_IMU_B1.7, U1.19 (GP14)
IMU_MOSI: J_IMU_A1.5, J_IMU_B1.5, R42.2
IMU_MOSI_MCU: R42.1, U1.12 (GP9)
IMU_SCLK: J_IMU_A1.3, J_IMU_B1.3, R41.2
IMU_SCLK_MCU: R41.1, U1.11 (GP8)
J_FORK_POT_GND: J_POT1.3, L_FORK_CMC1.2
J_FORK_WIPER: D2.1 (K), J_POT1.2, L_FORK_CMC1.3
J_SHOCK_POT_GND: J_POT1.5, L_SHOCK_CMC1.2
J_SHOCK_WIPER: D4.1 (K), J_POT1.4, L_SHOCK_CMC1.3
LDO_NRSS: C25.1, U_ANA_LDO1.14 (NR)
MCU_RUN: U1.30 (RUN)
OPA_D_OUT: U_AAF1.13 (-IND), U_AAF1.14 (OUTD)
POT_EXC: D3.1 (K), J_POT1.1, R34.2, R35.1, TP10.1
PSW_EN: Q_PWR2.1 (G), R_PWR2.1, R_PWR3.1, U_PWR1.4 (OUT)
PSW_GATE: Q_PWR1.1 (G), Q_PWR2.3 (D), R_PWR1.2
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
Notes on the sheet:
SST v2 — Suspension Telemetry Mainboard Greenfield revision (post-SBAS853A hardware review) Key signal-quality features: • TPS7A4700 ultra-low-noise LDO (4 µVrms) supplies +3V0_ANA for ADC + Pot • Decoupling per SBAS853A §10: 1 µF X7R on AVDD/DVDD, 220 nF on CAP — single GND plane (no AGND/DGND spl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
MCU — Pico 2 W (U1)
ADC — ADS131M02 (U2) — 2-ch 24-bit Σ∆, simultaneous
TCXO Y1 — 8.192 MHz HCMOS
U_AAF — OPA2333 dual op-amp (zero-drift) Voltage-follower Sallen-Key 2nd-order LPF per channel f_c ≈ 250 Hz, Q = 0.707 (R_SK1=R_SK2=22k, C_SK1=47n, C_SK2=22n) Gain = 1 — Spannungs-Attenuierung 2.5:1 erfolgt nachgelagert
POT-Anschluss & Eingangskette (Gain 0.4 overall) Pin1: +3V0_ANA via 47Ω + lokal 10µF/100nF/10nF Pin2: Wiper → CMC → R_SK1(22k) → SK-Node → R_SK2(22k) → OPA-IN+ → OPA_Out → R_atten1(1.5k 0.1%) → Atten-Node → R_filt_P(1k) → AIN_xP Pin3: VRef- → CMC → R_filt_N(1k) → AIN_xN (Kelvin) Atten-Node → R_atte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
U_ANA_LDO — TPS7A4700 ultra-low-noise LDO +3V3_DIG → +3V0_ANA (4 µVrms) Vout = 1.4 V + 1.6 V: pin 8 (1P6V) an GND, andere ANY-OUT offen NR = 10 nF (C25), EN = +3V3_DIG, SENSE an OUT Input: C22 10 µF an +3V3_DIG; Output: C6 22 µF an +3V0_ANA
POWER — LiPo → Q_RP1 → Q_PWR1 (Soft-Power MAX16150) → Schottky → VSYS +VBAT_SW → D_VSYS1 (PMEG3020EH) → VSYS (Pico) TPS7A4700: +3V3_DIG → +3V0_ANA
STORAGE / RTC / DISPLAY MicroSD J_SD on spi0 (GP16-19), VDD=+3V3_DIG DS3231 U3 on PIO-I2C (GP2/3), shared with OLED RTC_VBAT = CR1220 (BT1) direkt an U3 VBAT 4.7k pullups on DISP_SDA/SCL (mainboard, not OLED) OLED extern (J_OLED): SSD1306-Modul mit eigener Reg
IMU off-board connectors (4-pin JST-SH) i2c0 (GP8/9): Fork (0x6A, SA0=GND) + Rear (0x6B, SA0=VDD) i2c1 (GP14/15): Frame (0x6A, SA0=GND) + Handlebar (0x6B, upgrade) Bus pullups: 4.7k SDA/SCL each bus to +3V3_DIG (mainboard) INT1/INT2 nicht verdrahtet — Firmware pollt.
UI — Buttons + Buzzer + Debug BTN_L/R: TL3315NF160Q, 10k pullup zu +3V3_DIG, 100nF debounce Buzzer: differential drive (BUZ_DRV_A → 47Ω → BZ pin1; BUZ_DRV_B → 47Ω → BZ pin2) BUZ_DRV_A/B sind GP22/GP21 PWM Slice A/B mit B_INV Debug: UART Header 1x3 (GP1 RX / GP0 TX / GND)
Power Flags (drive ERC for power nets)
BOM POOL — Drag to final position in KiCad Generated by gen_passives.py All connections via global labels
Lader Li-Po (USB über Pico-Buchse, VBUS = Pico Pin 40). I_CHG = 1000 V / R_PROG = 300 mA. CHG_STAT: Teiler 10k/20k, 5 V -> 3,3 V an GP6. Laden = 0 V, fertig = 3,3 V.
Testpads (Unterseite, nicht bestückt) TP1..TP15: SMD-Pad D1,0 mm auf B.Cu, nicht in BOM/CPL
Soft-Power + Fuel-Gauge (Rev. 3, 2026-10-03) SW_L1 (Taster links) -> PWR_BTN -> U_PWR1 PB_IN (interner Pull-up 1,4 MOhm an VCC). BTN_L (GP4, R27 10k an +3V3_DIG) ueber D_PWR1 RB751S40 an PWR_BTN: Taste bleibt UI-Taste. U_PWR1 OUT -> PSW_EN -> Q_PWR2 -> PSW_GATE low -> Q_PWR1 (P-MOS) leitet: +VBAT -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
